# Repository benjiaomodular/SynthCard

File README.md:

# SynthCard
A businesscard-sized synthesizer module based on the Atari Punk Console.

I designed this project with the help of PCBWay. You can get a copy of these cards through the [PCBWay Shared Projects page](https://www.pcbway.com/project/shareproject/SynthCard_A_business_card_sized_synthesizer_module_84514b6e.html).

Schematics under `/KiCAD`. Gerber files under `/Fabrication`. Panel design under `/Inkscape`.

## Features

This module produces a pulse/square wave at 9Vpp.

There are two knobs. Knob 1 controls the frequency. Knob 2 controls the pulse width.

The module can be powered using a 9V power supply. A battery should work too.

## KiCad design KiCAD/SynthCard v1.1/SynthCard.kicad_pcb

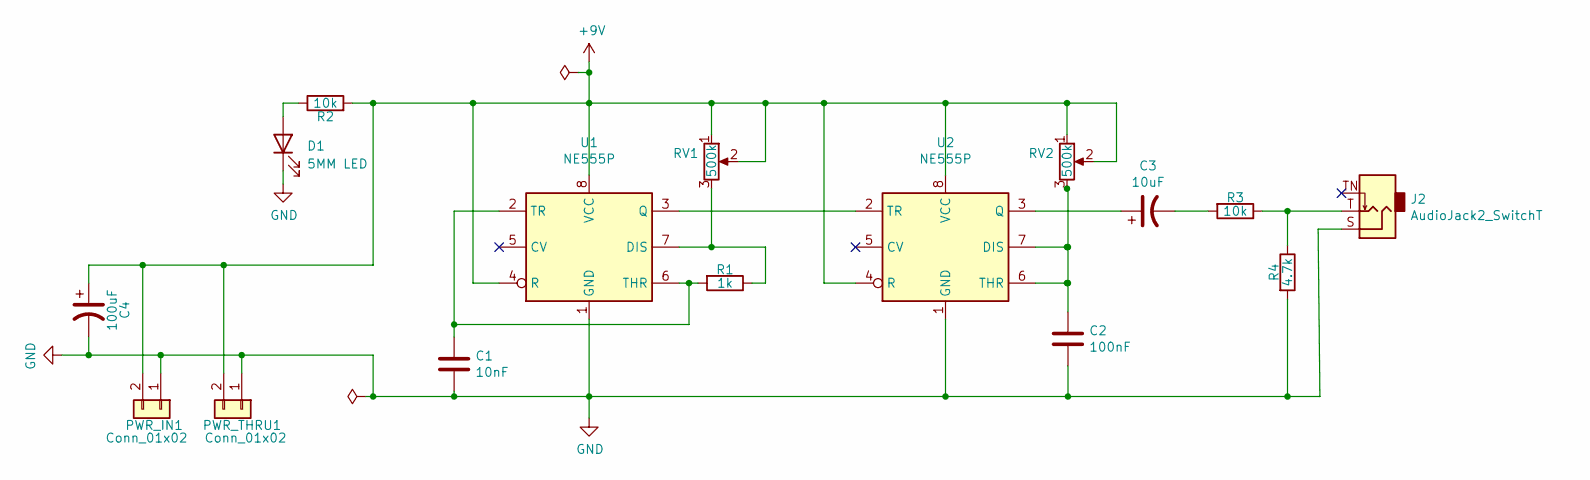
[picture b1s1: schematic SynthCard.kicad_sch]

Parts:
C1: 10nF; Capacitor_Rect_L7.2mm_W2.5mm_P5.00mm; Manufacturers Part Numb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 MMK5103K50J01L4BULK
C2: 100nF; Capacitor_Rect_L7.2mm_W2.5mm_P5.00mm; Manufacturers Part Numb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 MMK5104K50J01L4BULK
C3: 10uF; Capacitor_Radial_D5.0mm_P2.5mm; Manufacturers Part Numb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 UVR1E100MDD1TD
C4: 100uF; Capacitor_Radial_D5.0mm_P2.5mm; Manufacturers Part Numb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 UVR1E100MDD1TD
D1: 5MM LED; LED_D5.0mm
J2: AudioJack2_SwitchT; AudioJack_3.5mm; Manufacturers Part Numb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 PJ-3001F
PWR_IN1: Conn_01x02; PinSocket_1x02_P2.54mm_Vertical
PWR_THRU1: Conn_01x02; PinSocket_1x02_P2.54mm_Vertical
R1: 1k; Resistor_L6.3mm_D2.5mm_P7.62mm_Horizontal; Manufacturers Part Numb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 MF1/4DCT26A1001F
R2: 10k; Resistor_L6.3mm_D2.5mm_P7.62mm_Horizontal; Manufacturers Part Numb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 MF1/4DC1002F
R3: 10k; Resistor_L6.3mm_D2.5mm_P7.62mm_Horizontal; Manufacturers Part Numb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 MF1/4DCT26A1001F
R4: 4.7k; Resistor_L6.3mm_D2.5mm_P7.62mm_Horizontal; Manufacturers Part Numb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 MF1/4DCT26A1001F
RV1, RV2: 500k; Potentiometer_RV09; Manufacturers Part Numb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 RV09AF-40-20K-B500K
U1, U2: NE555P; DIP-8_W7.62mm; Manufacturers Part Numb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 NE555P

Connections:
+9V: C4.1, PWR_IN1.2, PWR_THRU1.2, R2.2, RV1.1, RV1.2, RV2.1, RV2.2, U1.4 (R), U1.8 (VCC), U2.4 (R), U2.8 (VCC)
GND: C1.2, C2.2, C4.2, D1.1 (K), J2.S, PWR_IN1.1, PWR_THRU1.1, R4.2, U1.1 (GND), U2.1 (GND)
unnamed: C1.1, R1.2, U1.2 (TR), U1.6 (THR)
unnamed: C2.1, RV2.3, U2.6 (THR), U2.7 (DIS)
unnamed: C3.1, U2.3 (Q)
unnamed: C3.2, R3.2
unnamed: D1.2 (A), R2.1
unnamed: J2.T, R3.1, R4.1
unnamed: R1.1, RV1.3, U1.7 (DIS)
unnamed: U1.3 (Q), U2.2 (TR)

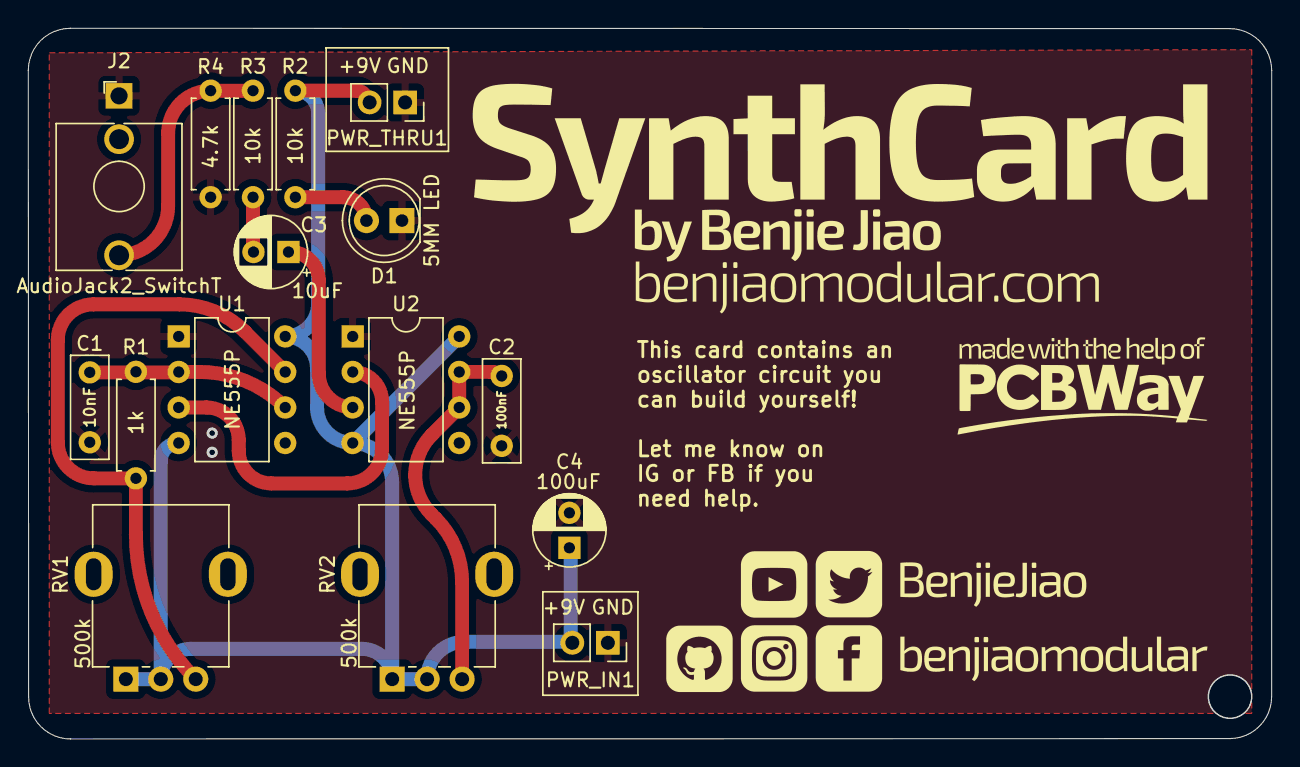
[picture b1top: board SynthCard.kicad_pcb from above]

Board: 2 copper layers, 88.9 x 50.8 mm, 16 parts (0 on the bottom side), 10 nets.

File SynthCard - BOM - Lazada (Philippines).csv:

Reference,Quantity,Value,Part Description,Lazada
BT1,1,Battery,9V Battery Snap or Barrel Connector,https://www.lazada.com.ph/products/10-pcs-3-terminal-solderi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
C1,1,10nF,Film Capacitors 50volts 0.01uF 10% LS 5mm,https://www.lazada.com.ph/products/polyester-film-capacitor-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
C2,1,100nF,Film Capacitors 50volts 0.1uF 10% LS 5mm,https://www.lazada.com.ph/products/polyester-film-capacitor-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
C3,1,10uF,Aluminum Electrolytic Capacitors - Radial Leaded 25volts 10uF,https://www.lazada.com.ph/products/aluminum-electrolytic-cap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
D1,1,5MM LED,"Standard 5MM LED, any color will do",https://www.lazada.com.ph/products/20pcs-pack-3mm-5mm-led-li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
J2,1,3.5mm Audio Jack,3.5mm Mono Jack,https://www.lazada.com.ph/products/50pcs-35mm-female-audio-c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
R1,1,1k,1/4W Resistor 1k ohms,https://www.lazada.com.ph/products/50pcs-1k-ohms-14w-metal-f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
R2,1,10k,1/4W Resistor 10k ohms,https://www.lazada.com.ph/products/50pcs-10k-ohms-14w-metal-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
RV1 RV2,2,500k,500k Potentiometers. Also try 100k and 1M for different response and range.,https://www.lazada.com.ph/products/5set10pcs-rv09-vertical-1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
U1 U2,2,NE555P,Timers & Support Products,https://www.lazada.com.ph/products/diymore-10pcs50pcs-lot-ne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

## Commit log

2022-06-21 added readme
2022-10-11 Tried inkscape
2022-11-01 First production version
2022-11-01 Typo on naming
2022-11-01 Added a photo of the synthcard
2022-11-01 Added MIT License file
2022-11-01 Added working bom
2022-11-08 Added BOM for Lazada
2022-11-08 removed csv from gitignore
2022-11-08 Added lazada link for BOM
2022-11-08 Added wires to bom
2023-11-16 ADded build guide
2023-12-29 Added workshop slides
